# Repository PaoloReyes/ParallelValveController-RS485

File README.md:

# Parallel Valve Controller RS485 - README

## Overview
This repository contains the hardware and software needed to build a 20 container controller under freertos SMP multicore architecture on UART ISR event driven processes for ESP32-S3.
The controller is responsible for listening to RS485 messages and actuate the connected containers accordingly.

## Features
- **Parallel Control**: Uses two XTensa LX7 Cores under freertos on container independent tasks.
- **Reduces PLC overhead**: PID control is performed under the ESP32-S3 and not the main PLC logic.
- **Communication**: Interfaces with the main controller via RS485 communication.

## Communication Protocol
The car module receives and sends commands via a predefined protocol:
- `OP #` - Opens the controller based on its id number #.
- `CL` - Immediately closes the RS485 communication with the controller.
- `AD` - Returns the current id of the controller.
- `AD #` - Assigns the number # as the controller id.
- `WP` - Makes the AD # command to take effect and needs a reboot.
- `CV #1 #2 #3` - Performs a control update on the specified #1 container, #2 with the current weight and #3 the weight setpoint

## Hardware

## Software Architecture

## FSM

## Troubleshooting
| Issue                          | Possible Cause                           | Solution |
|--------------------------------|------------------------------------------|----------|
| Valve not moving               | Loose wiring, wrong valve firmware       | Check connections, update your valve firmware |
| Solenoid not actuating         | Loose wiring                             | Check connections |
| Motor not mixing               | Loose wiring                             | Check connections |
| Container weight not available | Loose wiring, wrong digitalizer firmware | Check connections, update your valve firmware 
| No response                    | Communication failure, wrong firmware    | Verify RS485 wiring and settings, update the controller firmware |

## Contributors
- **Paolo Reyes** - Lead Developer

## License
This project is licensed under the MIT License - see the LICENSE file for details.

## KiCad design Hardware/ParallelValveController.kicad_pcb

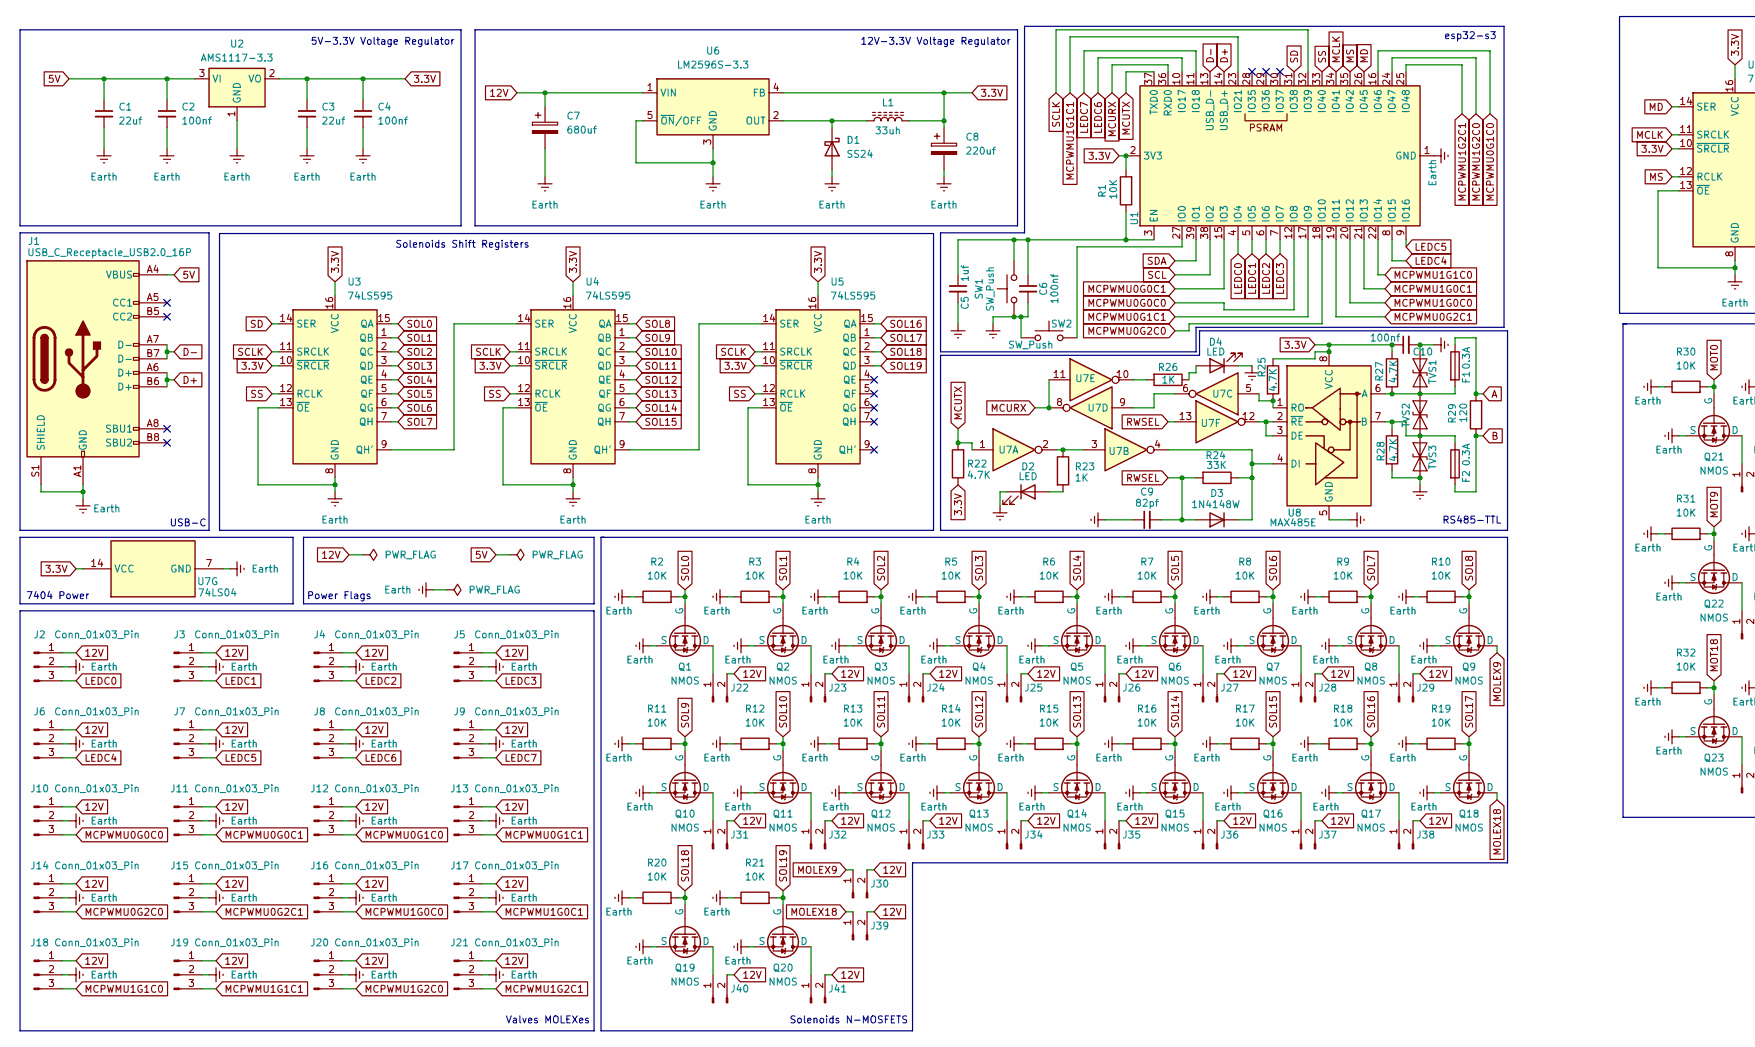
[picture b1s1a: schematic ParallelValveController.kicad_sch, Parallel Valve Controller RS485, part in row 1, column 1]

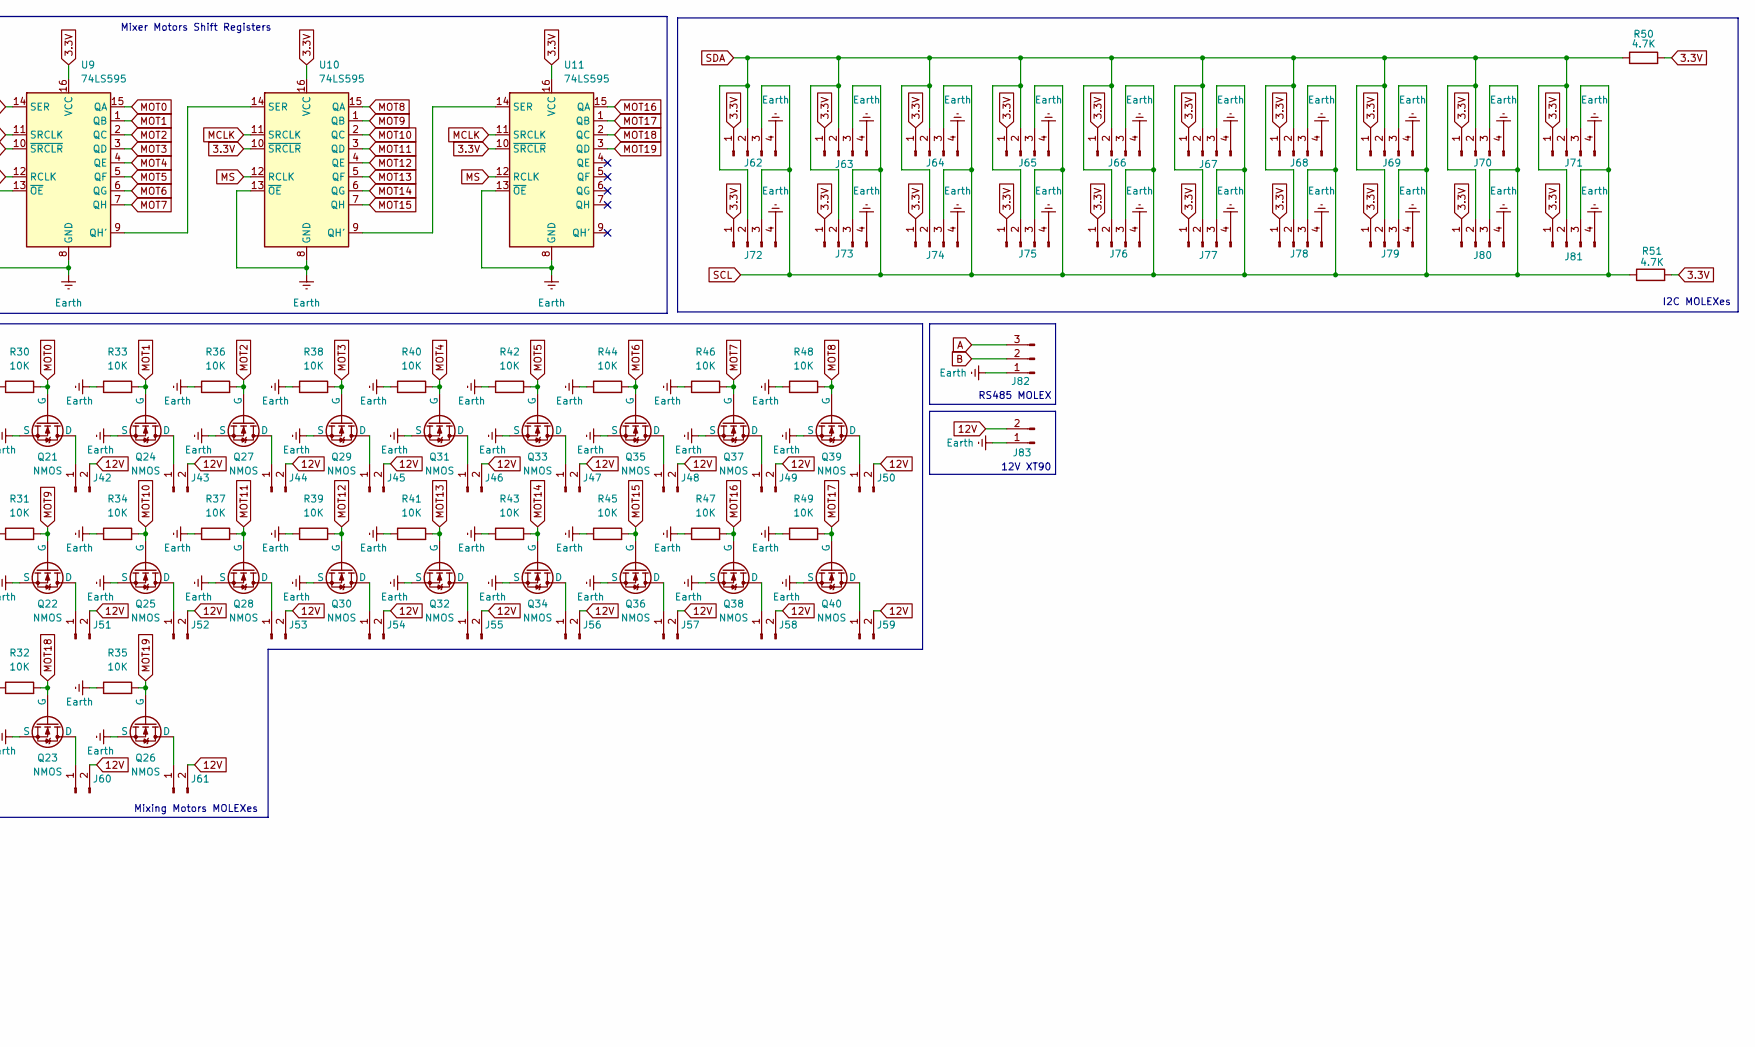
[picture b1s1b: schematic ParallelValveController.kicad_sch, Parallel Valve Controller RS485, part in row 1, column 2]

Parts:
C1, C3: 22uf; C_0805_2012Metric
C2, C4, C6, C10: 100nf; C_0805_2012Metric
C5: 1uf; C_0805_2012Metric
C7: 680uf; CP_Radial_D10.0mm_P5.00mm
C8: 220uf; CP_Elec_6.3x7.7
C9: 82pf; C_0805_2012Metric
D1: SS24; D_SMA
D2, D4: LED; LED_0805_2012Metric
D3: 1N4148W; D_SOD-123
F1, F2: 0.3A; Fuse_2010_5025Metric_Pad1.52x2.65mm_HandSolder
J1: USB_C_Receptacle_USB2.0_16P; USB_C_Receptacle_HRO_TYPE-C-31-M-12
J2, J3, J4, J5, J6, J7, J8, J9, J10, J11, J12, J13, J14, J15, J16, J17, J18, J19, J20, J21, J82: Conn_01x03_Pin; Molex_KK-254_AE-6410-03A_1x03_P2.54mm_Vertical
J22, J23, J24, J25, J26, J27, J28, J29, J30, J31, J32, J33, J34, J35, J36, J37, J38, J39, J40, J41, J42, J43, J44, J45, J46, J47, J48, J49, J50, J51, J52, J53, J54, J55, J56, J57, J58, J59, J60, J61: Conn_01x02_Pin; Molex_KK-254_AE-6410-02A_1x02_P2.54mm_Vertical
J62, J63, J64, J65, J66, J67, J68, J69, J70, J71, J72, J73, J74, J75, J76, J77, J78, J79, J80, J81: Conn_01x02_Pin; Molex_KK-254_AE-6410-04A_1x04_P2.54mm_Vertical
J83: Conn_01x02_Pin; XT90-Female
L1: 33uh; L_12x12mm_H8mm
Q1, Q2, Q3, Q4, Q5, Q6, Q7, Q8, Q9, Q10, Q11, Q12, Q13, Q14, Q15, Q16, Q17, Q18, Q19, Q20, Q21, Q22, Q23, Q24, Q25, Q26, Q27, Q28, Q29, Q30, Q31, Q32, Q33, Q34, Q35, Q36, Q37, Q38, Q39, Q40: NMOS; SI2302
R1, R2, R3, R4, R5, R6, R7, R8, R9, R10, R11, R12, R13, R14, R15, R16, R17, R18, R19, R20, R21, R30, R31, R32, R33, R34, R35, R36, R37, R38, R39, R40, R41, R42, R43, R44, R45, R46, R47, R48, R49: 10K; R_0805_2012Metric
R22, R25, R27, R28, R50, R51: 4.7K; R_0805_2012Metric
R23, R26: 1K; R_0805_2012Metric
R24: 33K; R_0805_2012Metric
R29: 120; R_0805_2012Metric
SW1, SW2: SW_Push; MicroSwtich3x4x2mm
TVS1: SMAJ6.8CA; D_SMA
TVS2, TVS3: SMAJ6.5CA; D_SMA
U1: ESP32-S3-WROOM-1
U2: AMS1117-3.3; SOT-223-3_TabPin2
U3, U4, U5, U9, U10, U11: 74LS595; SOP-16_3.9x9.9mm_P1.27mm
U6: LM2596S-3.3; TO-263-5_TabPin3
U7: 74LS04; SO-14_5.3x10.2mm_P1.27mm
U8: MAX485E; SOP-8_3.9x4.9mm_P1.27mm

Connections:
3.3V: C3.1, C4.1, C8.1, C10.1, J62.1, J63.1, J64.1, J65.1, J66.1, J67.1, J68.1, J69.1, J70.1, J71.1, J72.1, J73.1, J74.1, J75.1, J76.1, J77.1, J78.1, J79.1, J80.1, J81.1, L1.2, R1.2, R22.1, R25.1, R27.1, R50.2, R51.2, U1.2 (3V3), U2.2 (VO), U3.10 (~SRCLR), U3.16 (VCC), U4.10 (~SRCLR), U4.16 (VCC), U5.10 (~SRCLR), U5.16 (VCC), U6.4 (FB), U7.14 (VCC), U8.8 (VCC), U9.10 (~SRCLR), U9.16 (VCC), U10.10 (~SRCLR), U10.16 (VCC), U11.10 (~SRCLR), U11.16 (VCC)
5V: C1.1, C2.1, J1.A4 (VBUS), J1.A9 (VBUS), J1.B4 (VBUS), J1.B9 (VBUS), U2.3 (VI)
12V: C7.1, J2.1, J3.1, J4.1, J5.1, J6.1, J7.1, J8.1, J9.1, J10.1, J11.1, J12.1, J13.1, J14.1, J15.1, J16.1, J17.1, J18.1, J19.1, J20.1, J21.1, J22.2, J23.2, J24.2, J25.2, J26.2, J27.2, J28.2, J29.2, J30.2, J31.2, J32.2, J33.2, J34.2, J35.2, J36.2, J37.2, J38.2, J39.2, J40.2, J41.2, J42.2, J43.2, J44.2, J45.2, J46.2, J47.2, J48.2, J49.2, J50.2, J51.2, J52.2, J53.2, J54.2, J55.2, J56.2, J57.2, J58.2, J59.2, J60.2, J61.2, J83.2, U6.1 (VIN)
A: F1.1, J82.3, R29.2
B: F2.2, J82.2, R29.1
D+: J1.A6 (D+), J1.B6 (D+), U1.14 (USB_D+)
D-: J1.A7 (D-), J1.B7 (D-), U1.13 (USB_D-)
Earth: C1.2, C2.2, C3.2, C4.2, C5.2, C6.2, C7.2, C8.2, C9.1, C10.2, D1.2 (A), D2.1 (K), D4.1 (K), J1.A1 (GND), J1.A12 (GND), J1.B1 (GND), J1.B12 (GND), J1.S1 (SHIELD), J2.2, J3.2, J4.2, J5.2, J6.2, J7.2, J8.2, J9.2, J10.2, J11.2, J12.2, J13.2, J14.2, J15.2, J16.2, J17.2, J18.2, J19.2, J20.2, J21.2, J62.4, J63.4, J64.4, J65.4, J66.4, J67.4, J68.4, J69.4, J70.4, J71.4, J72.4, J73.4, J74.4, J75.4, J76.4, J77.4, J78.4, J79.4, J80.4, J81.4, J82.1, J83.1, Q1.3 (S), Q2.3 (S), Q3.3 (S), Q4.3 (S), Q5.3 (S), Q6.3 (S), Q7.3 (S), Q8.3 (S), Q9.3 (S), Q10.3 (S), Q11.3 (S), Q12.3 (S), Q13.3 (S), Q14.3 (S), Q15.3 (S), Q16.3 (S), Q17.3 (S), Q18.3 (S), Q19.3 (S), Q20.3 (S), Q21.3 (S), Q22.3 (S), Q23.3 (S), Q24.3 (S), Q25.3 (S), Q26.3 (S), Q27.3 (S), Q28.3 (S), Q29.3 (S), Q30.3 (S), Q31.3 (S), Q32.3 (S), Q33.3 (S), Q34.3 (S), Q35.3 (S), Q36.3 (S), Q37.3 (S), Q38.3 (S), Q39.3 (S), Q40.3 (S), R2.1, R3.1, R4.1, R5.1, R6.1, R7.1, R8.1, R9.1, R10.1, R11.1, R12.1, R13.1, R14.1, R15.1, R16.1, R17.1, R18.1, R19.1, R20.1, R21.1, R28.2, R30.1, R31.1, R32.1, R33.1, R34.1, R35.1, R36.1, R37.1, R38.1, R39.1, R40.1, R41.1, R42.1, R43.1, R44.1, R45.1, R46.1, R47.1, R48.1, R49.1, SW1.1, SW2.1, TVS1.2 (A2), TVS3.1 (A1), U1.1 (GND), U1.40 (GND), U1.41 (GND), U2.1 (GND), U3.8 (GND), U3.13 (~OE), U4.8 (GND), U4.13 (~OE), U5.8 (GND), U5.13 (~OE), U6.3 (GND), U6.5 (~ON/OFF), U7.7 (GND), U8.5 (GND), U9.8 (GND), U9.13 (~OE), U10.8 (GND), U10.13 (~OE), U11.8 (GND), U11.13 (~OE)
LEDC0: J2.3, U1.4 (IO4)
LEDC1: J3.3, U1.5 (IO5)
LEDC2: J4.3, U1.6 (IO6)
LEDC3: J5.3, U1.7 (IO7)
LEDC4: J6.3, U1.8 (IO15)
LEDC5: J7.3, U1.9 (IO16)
LEDC6: J8.3, U1.10 (IO17)
LEDC7: J9.3, U1.11 (IO18)
MCLK: U1.34 (IO41), U9.11 (SRCLK), U10.11 (SRCLK), U11.11 (SRCLK)
MCPWMU0G0C0: J10.3, U1.12 (IO8)
MCPWMU0G0C1: J11.3, U1.15 (IO3)
MCPWMU0G1C0: J12.3, U1.16 (IO46)
MCPWMU0G1C1: J13.3, U1.17 (IO9)
MCPWMU0G2C0: J14.3, U1.18 (IO10)
MCPWMU0G2C1: J15.3, U1.19 (IO11)
MCPWMU1G0C0: J16.3, U1.20 (IO12)
MCPWMU1G0C1: J17.3, U1.21 (IO13)
MCPWMU1G1C0: J18.3, U1.22 (IO14)
MCPWMU1G1C1: J19.3, U1.23 (IO21)
MCPWMU1G2C0: J20.3, U1.24 (IO47)
MCPWMU1G2C1: J21.3, U1.25 (IO48)
MCURX: U1.36 (RXD0), U7.8, U7.11
MCUTX: R22.2, U1.37 (TXD0), U7.1
MD: U1.26 (IO45), U9.14 (SER)
MOLEX9: J30.1, Q9.1 (D)
MOLEX18: J39.1, Q18.1 (D)
MOT0: Q21.2 (G), R30.2, U9.15 (QA)
MOT1: Q24.2 (G), R33.2, U9.1 (QB)
MOT2: Q27.2 (G), R36.2, U9.2 (QC)
MOT3: Q29.2 (G), R38.2, U9.3 (QD)
MOT4: Q31.2 (G), R40.2, U9.4 (QE)
MOT5: Q33.2 (G), R42.2, U9.5 (QF)
MOT6: Q35.2 (G), R44.2, U9.6 (QG)
MOT7: Q37.2 (G), R46.2, U9.7 (QH)
MOT8: Q39.2 (G), R48.2, U10.15 (QA)
MOT9: Q22.2 (G), R31.2, U10.1 (QB)
MOT10: Q25.2 (G), R34.2, U10.2 (QC)
MOT11: Q28.2 (G), R37.2, U10.3 (QD)
MOT12: Q30.2 (G), R39.2, U10.4 (QE)
MOT13: Q32.2 (G), R41.2, U10.5 (QF)
MOT14: Q34.2 (G), R43.2, U10.6 (QG)
MOT15: Q36.2 (G), R45.2, U10.7 (QH)
MOT16: Q38.2 (G), R47.2, U11.15 (QA)
MOT17: Q40.2 (G), R49.2, U11.1 (QB)
MOT18: Q23.2 (G), R32.2, U11.2 (QC)
MOT19: Q26.2 (G), R35.2, U11.3 (QD)
MS: U1.35 (IO42), U9.12 (RCLK), U10.12 (RCLK), U11.12 (RCLK)
unnamed: D1.1 (K), L1.1, U6.2 (OUT)
unnamed: D2.2 (A), R23.2
unnamed: D3.1 (K), R24.1, U7.4, U8.4 (DI)
unnamed: D4.2 (A), R26.1
unnamed: J22.1, Q1.1 (D)
unnamed: J23.1, Q2.1 (D)
unnamed: J24.1, Q3.1 (D)
unnamed: J25.1, Q4.1 (D)
unnamed: J26.1, Q5.1 (D)
unnamed: J27.1, Q6.1 (D)
unnamed: J28.1, Q7.1 (D)
unnamed: J29.1, Q8.1 (D)
unnamed: J31.1, Q10.1 (D)
unnamed: J32.1, Q11.1 (D)
unnamed: J33.1, Q12.1 (D)
unnamed: J34.1, Q13.1 (D)
unnamed: J35.1, Q14.1 (D)
unnamed: J36.1, Q15.1 (D)
unnamed: J37.1, Q16.1 (D)
unnamed: J38.1, Q17.1 (D)
unnamed: J40.1, Q19.1 (D)
unnamed: J41.1, Q20.1 (D)
unnamed: J42.1, Q21.1 (D)
unnamed: J43.1, Q24.1 (D)
unnamed: J44.1, Q27.1 (D)
unnamed: J45.1, Q29.1 (D)
unnamed: J46.1, Q31.1 (D)
unnamed: J47.1, Q33.1 (D)
unnamed: J48.1, Q35.1 (D)
unnamed: J49.1, Q37.1 (D)
unnamed: J50.1, Q39.1 (D)
unnamed: J51.1, Q22.1 (D)
unnamed: J52.1, Q25.1 (D)
unnamed: J53.1, Q28.1 (D)
unnamed: J54.1, Q30.1 (D)
unnamed: J55.1, Q32.1 (D)
unnamed: J56.1, Q34.1 (D)
unnamed: J57.1, Q36.1 (D)
unnamed: J58.1, Q38.1 (D)
unnamed: J59.1, Q40.1 (D)
unnamed: J60.1, Q23.1 (D)
unnamed: J61.1, Q26.1 (D)
unnamed: R23.1, U7.2, U7.3
unnamed: R26.2, U7.10
unnamed: F1.2, R27.2, TVS1.1 (A1), TVS2.2 (A2), U8.6 (A)
unnamed: F2.1, R28.1, TVS2.1 (A1), TVS3.2 (A2), U8.7 (B)
unnamed: C5.1, C6.1, R1.1, SW1.2, U1.3 (EN)
unnamed: SW2.2, U1.27 (IO0)
unnamed: U3.9 (QH'), U4.14 (SER)
unnamed: U4.9 (QH'), U5.14 (SER)
unnamed: U7.6, U7.9
unnamed: U7.12, U8.2 (~RE), U8.3 (DE)
unnamed: R25.2, U7.5, U8.1 (RO)
unnamed: U10.9 (QH'), U11.14 (SER)
unnamed: U9.9 (QH'), U10.14 (SER)
RWSEL: C9.2, D3.2 (A), R24.2, U7.13
SCL: J62.3, J63.3, J64.3, J65.3, J66.3, J67.3, J68.3, J69.3, J70.3, J71.3, J72.3, J73.3, J74.3, J75.3, J76.3, J77.3, J78.3, J79.3, J80.3, J81.3, R51.1, U1.38 (IO2)
SCLK: U1.32 (IO39), U3.11 (SRCLK), U4.11 (SRCLK), U5.11 (SRCLK)
SD: U1.31 (IO38), U3.14 (SER)
SDA: J62.2, J63.2, J64.2, J65.2, J66.2, J67.2, J68.2, J69.2, J70.2, J71.2, J72.2, J73.2, J74.2, J75.2, J76.2, J77.2, J78.2, J79.2, J80.2, J81.2, R50.1, U1.39 (IO1)
SOL0: Q1.2 (G), R2.2, U3.15 (QA)
SOL1: Q2.2 (G), R3.2, U3.1 (QB)
SOL2: Q3.2 (G), R4.2, U3.2 (QC)
SOL3: Q4.2 (G), R5.2, U3.3 (QD)
SOL4: Q5.2 (G), R6.2, U3.4 (QE)
SOL5: Q6.2 (G), R7.2, U3.5 (QF)
SOL6: Q7.2 (G), R8.2, U3.6 (QG)
SOL7: Q8.2 (G), R9.2, U3.7 (QH)
SOL8: Q9.2 (G), R10.2, U4.15 (QA)
SOL9: Q10.2 (G), R11.2, U4.1 (QB)
SOL10: Q11.2 (G), R12.2, U4.2 (QC)
SOL11: Q12.2 (G), R13.2, U4.3 (QD)
SOL12: Q13.2 (G), R14.2, U4.4 (QE)
SOL13: Q14.2 (G), R15.2, U4.5 (QF)
SOL14: Q15.2 (G), R16.2, U4.6 (QG)
SOL15: Q16.2 (G), R17.2, U4.7 (QH)
SOL16: Q17.2 (G), R18.2, U5.15 (QA)
SOL17: Q18.2 (G), R19.2, U5.1 (QB)
SOL18: Q19.2 (G), R20.2, U5.2 (QC)
SOL19: Q20.2 (G), R21.2, U5.3 (QD)
SS: U1.33 (IO40), U3.12 (RCLK), U4.12 (RCLK), U5.12 (RCLK)

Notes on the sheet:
Solenoids Shift Registers
USB-C
RS485-TTL
Mixer Motors Shift Registers
RS485 MOLEX
12V XT90
esp32-s3
Valves MOLEXes
Mixing Motors MOLEXes
7404 Power
I2C MOLEXes
Power Flags
5V-3.3V Voltage Regulator
12V-3.3V Voltage Regulator
Solenoids N-MOSFETS

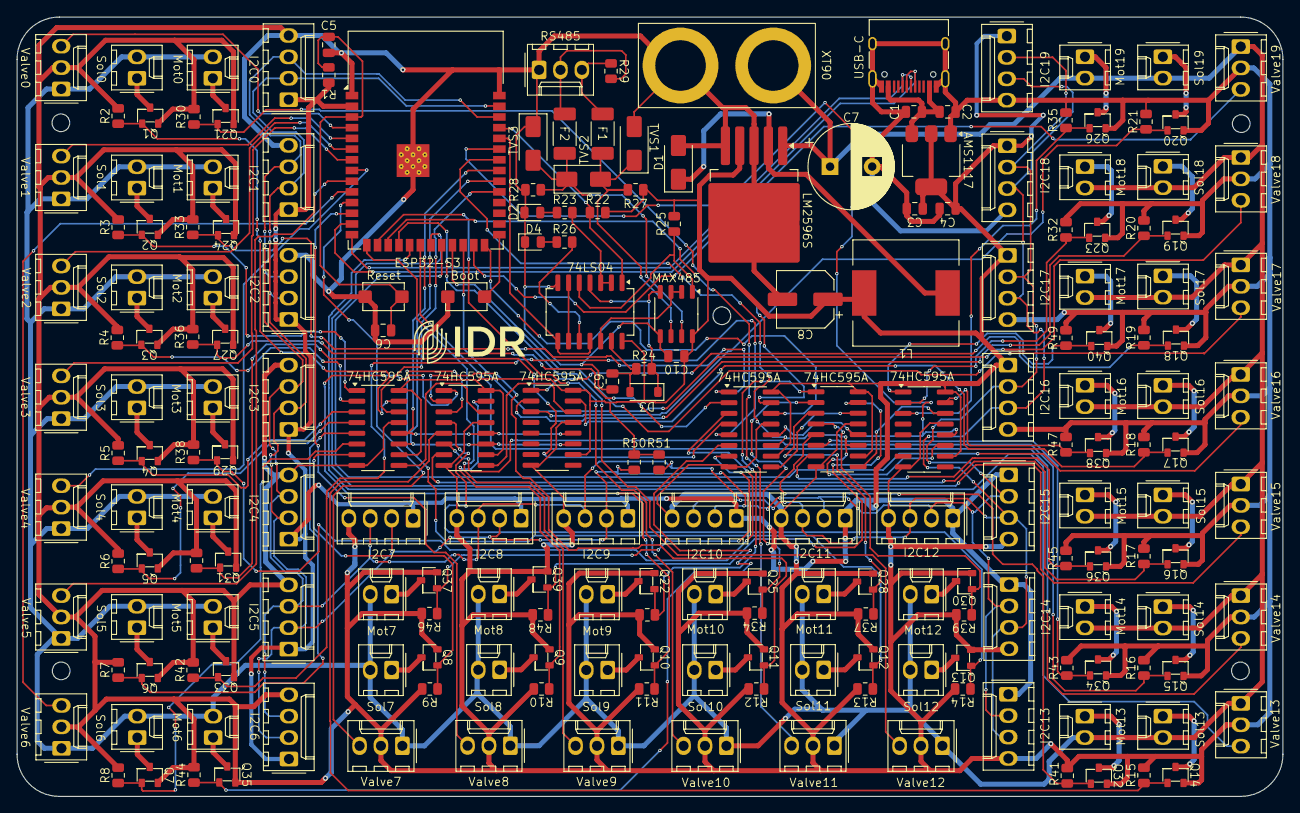
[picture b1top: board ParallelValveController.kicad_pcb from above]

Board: 2 copper layers, 150.2 x 92.5 mm, 207 parts (0 on the bottom side), 136 nets.

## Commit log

2025-03-04 feat(Release): UART FSM and multicore tasks infrastructure
2025-03-05 feat(PID Tasks): Task Notifications to PID tasks
2025-03-05 feat(PID Tasks): Infrastructure to output pwm from ledc module via second param on task notifications
2025-03-06 feat(mcpwm): Infrastructure to output pwm from mcpwm unit 0
2025-03-06 feat(PID): Added support for mcpwm on 12 new PID Tasks
2025-03-06 feat(PID): Added pid controller for each task
2025-03-06 fix(ESP_ERROR_CHECK): Added some ESP_ERROR_CHECKS on missing functions
2025-03-16 feat(Hardware): Hardware implementation
2025-03-16 feat(Architecture): Architecture added to readme
2025-03-17 feat(FSM): Added FSM logic
2025-03-17 fix(FSM): Fix FSM logic
2025-03-23 general update
2025-03-26 fix(rs485): logic rs485 fixed for invalid op
